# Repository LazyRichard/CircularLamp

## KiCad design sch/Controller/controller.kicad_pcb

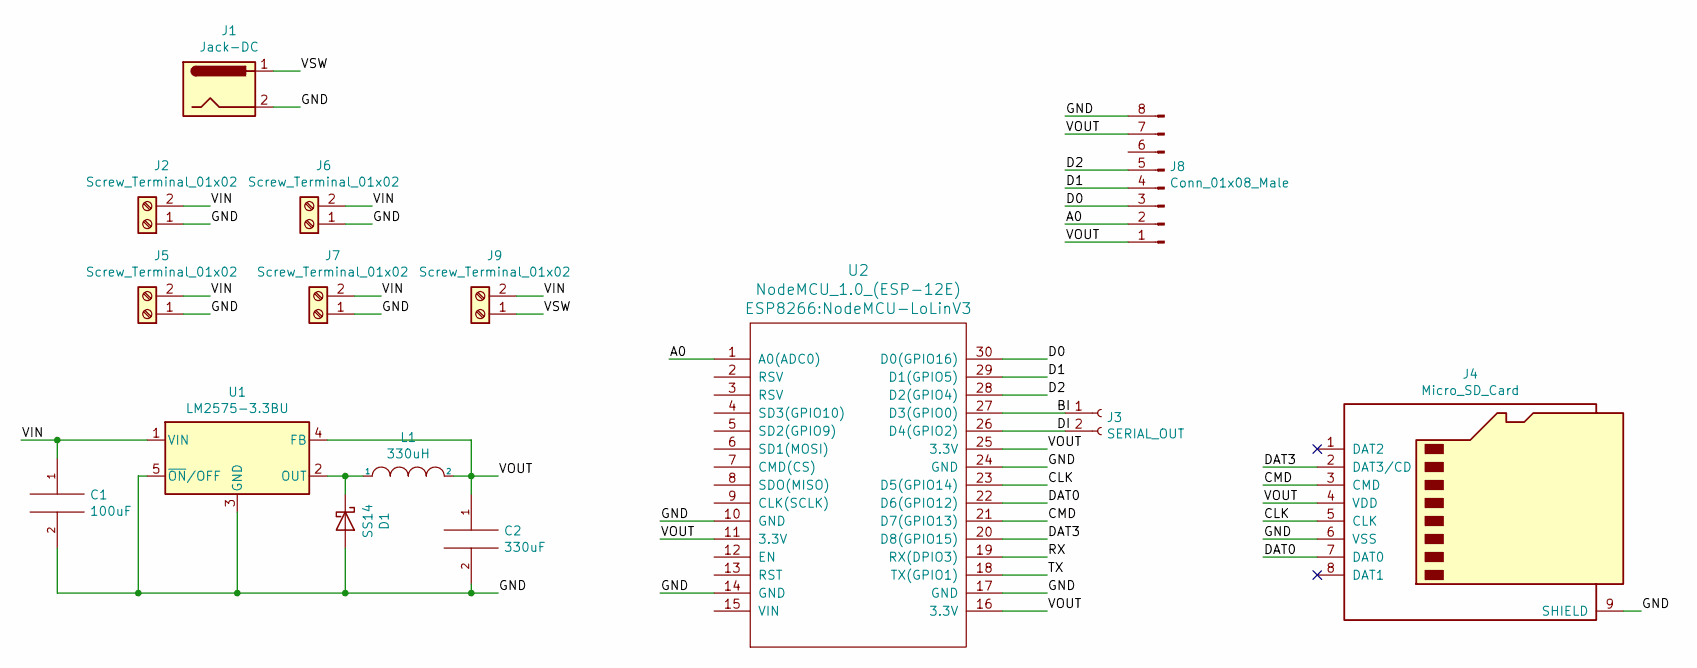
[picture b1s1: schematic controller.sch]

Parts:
C1: 100uF; CP_Radial_D8.0mm_P3.50mm
C2: 330uF; CP_Radial_D8.0mm_P3.50mm
D1: SS14; D_SMA_Handsoldering
J1: Jack-DC; BarrelJack_Horizontal
J2, J5, J6, J7, J9: Screw_Terminal_01x02; PAD-2
J3: SERIAL_OUT; PinHeader_1x02_P2.54mm_Vertical
J4: Micro_SD_Card; MSDC-M61408
J8: Conn_01x08_Male; PinHeader_1x08_P2.54mm_Vertical
L1: 330uH; L_Taiyo-Yuden_NR-50xx_HandSoldering
U1: LM2575-3.3BU; TO-263-5_TabPin3
U2: NodeMCU_1.0_(ESP-12E); NodeMCU-LoLinV3

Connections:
/A0: J8.2, U2.1 (A0(ADC0))
/BI: J3.1, U2.27 (D3(GPIO0))
/CLK: J4.5 (CLK), U2.23 (D5(GPIO14))
/CMD: J4.3 (CMD), U2.21 (D7(GPIO13))
/D0: J8.3, U2.30 (D0(GPIO16))
/D1: J8.4, U2.29 (D1(GPIO5))
/D2: J8.5, U2.28 (D2(GPIO4))
/DAT0: J4.7 (DAT0), U2.22 (D6(GPIO12))
/DAT3: J4.2 (DAT3/CD), U2.20 (D8(GPIO15))
/DI: J3.2, U2.26 (D4(GPIO2))
/GND: C1.2, C2.2, D1.2 (A), J1.2, J1.3, J2.1, J4.6 (VSS), J4.9 (SHIELD), J5.1, J6.1, J7.1, J8.8, U1.3 (GND), U1.5 (~ON~/OFF), U2.10 (GND), U2.14 (GND), U2.17 (GND), U2.24 (GND)
/RX: U2.19 (RX(DPIO3))
/TX: U2.18 (TX(GPIO1))
/VIN: C1.1, J2.2, J5.2, J6.2, J7.2, J9.2, U1.1 (VIN)
/VOUT: C2.1, J4.4 (VDD), J8.1, J8.7, L1.2, U1.4 (FB), U2.11 (3.3V), U2.16 (3.3V), U2.25 (3.3V)
/VSW: J1.1, J9.1
unnamed: D1.1 (K), L1.1, U1.2 (OUT)

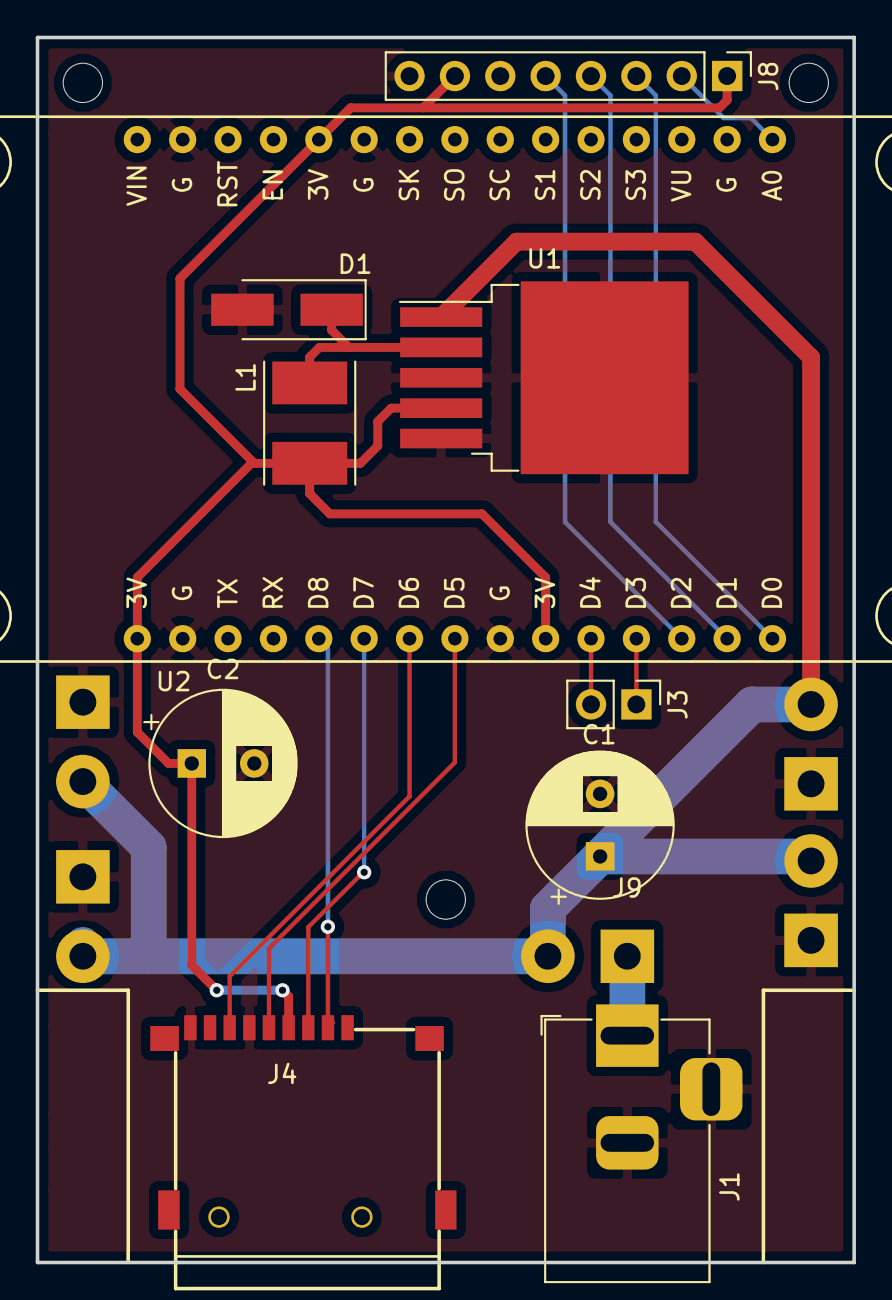
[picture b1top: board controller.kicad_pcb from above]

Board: 2 copper layers, 45.7 x 68.6 mm, 15 parts (0 on the bottom side), 15 nets.

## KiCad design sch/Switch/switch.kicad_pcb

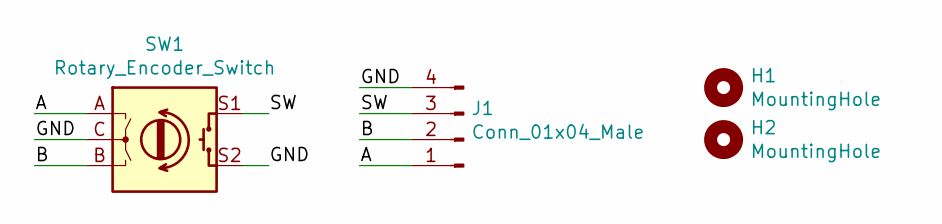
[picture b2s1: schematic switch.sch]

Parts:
H1, H2: MountingHole; MountingHole_2.2mm_M2
J1: Conn_01x04_Male; PinHeader_1x04_P2.54mm_Vertical
SW1: Rotary_Encoder_Switch; EC12B24S2033ZZZ

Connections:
/A: J1.1, SW1.A
/B: J1.2, SW1.B
/GND: J1.4, SW1.C, SW1.S2
/SW: J1.3, SW1.S1

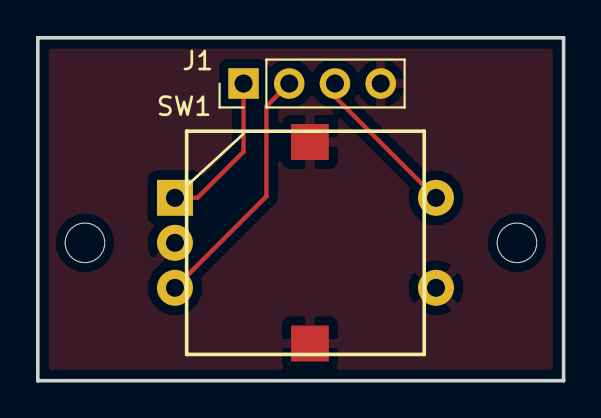
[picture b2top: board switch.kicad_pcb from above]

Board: 2 copper layers, 29.2 x 19.0 mm, 4 parts (0 on the bottom side), 4 nets.

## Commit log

2019-04-09 hello nodemcu
2019-04-15 basic functional test
2019-04-17 update encoder test
2019-04-17 add basic func
2019-04-19 add basic function test
2019-04-19 add fade animation
2019-04-19 add some animation set
2019-04-19 support multiple animations
2019-04-19 fix update current time
2019-04-19 fix button event
2019-04-19 fix button event2
2019-04-19 remove binary file
2019-04-19 debounce button event
2019-04-19 add zminorandom animation
2019-04-19 optimize animations variable
2019-04-19 fix serial message
2019-04-19 tuning min brightness value
2019-04-20 serial event to loop
2019-04-20 fix tileRandomAnimation isn't catch previous pixel color
2019-04-20 fix zTetrominoRandomAnimation limits
2019-04-20 fix serial debug msg format
2019-04-20 fix tileRandomAnimation limits.....
2019-04-20 apply fadeoutAnimation easing
2020-01-27 remove binary
2020-01-27 add kicad
